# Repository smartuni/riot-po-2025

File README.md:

## GitFlow

 - [GitFlow Document] (/.github/GitFlow)

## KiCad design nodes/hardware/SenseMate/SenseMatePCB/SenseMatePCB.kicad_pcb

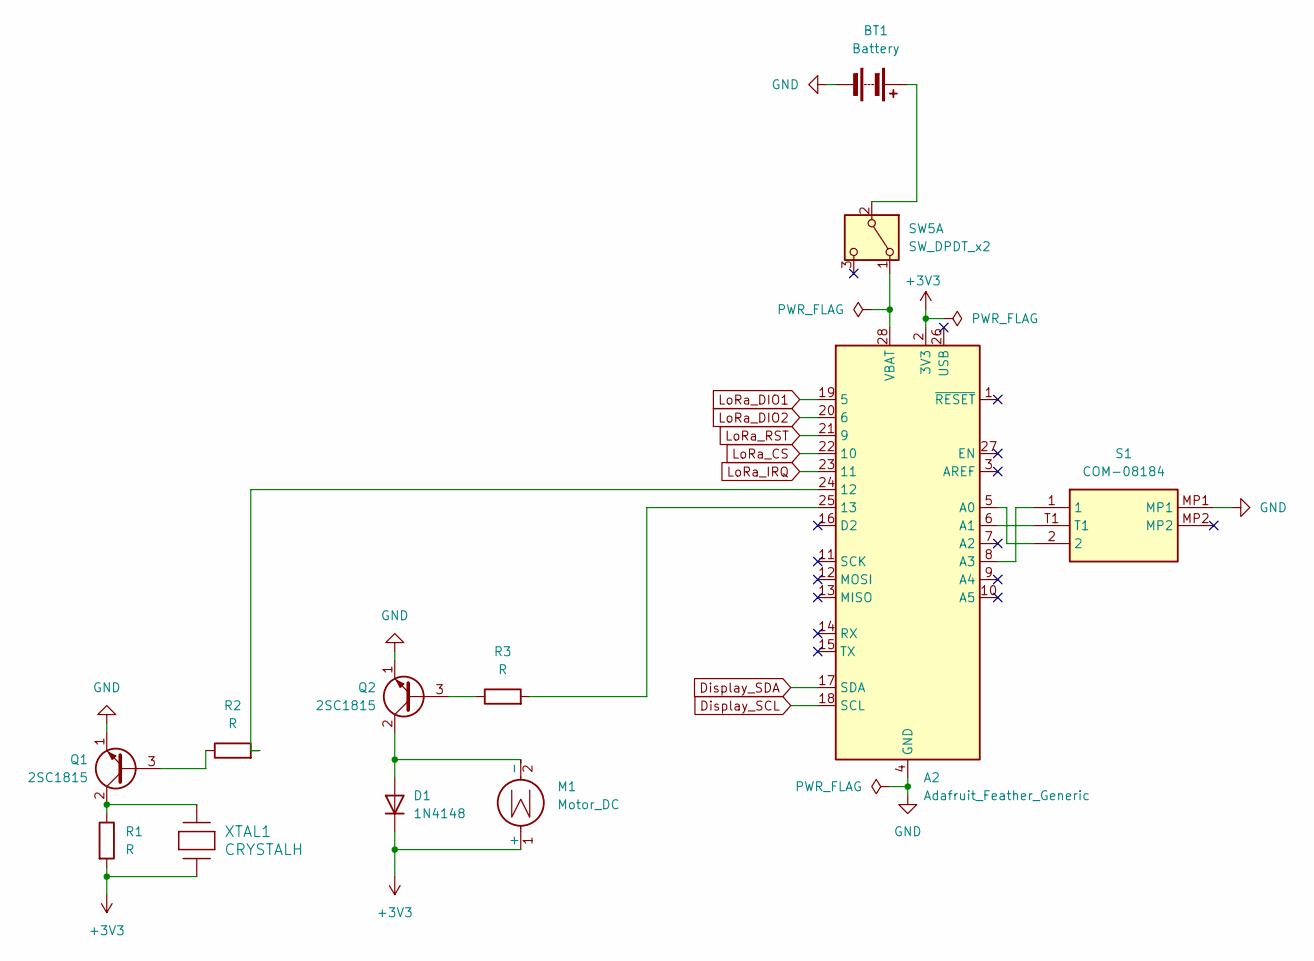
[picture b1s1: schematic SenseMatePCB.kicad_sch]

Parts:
A2: Adafruit_Feather_Generic; Adafruit_Feather_Sense
BT1: Battery; JST_PH_S2B-PH-K_1x02_P2.00mm_Horizontal
D1: 1N4148; D_DO-35_SOD27_P7.62mm_Horizontal
M1: Motor_DC; JST_PH_S2B-PH-K_1x02_P2.00mm_Horizontal
Q1, Q2: 2SC1815; TO-92_Inline
R1, R2, R3: R; R_0805_2012Metric
S1: COM-08184; COM08184; Manufacturer_Part_Number COM-08184
SW5: SW_DPDT_x2; OS102011MA1QN1
XTAL1: CRYSTALH; XTAL_PS1240P02BT_TDK

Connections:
+3V3: A2.2 (3V3), D1.1 (K), M1.1 (+), R1.2, XTAL1.1; also elsewhere on the board
GND: A2.4 (GND), BT1.2 (-), Q1.1 (E), Q2.1 (E), S1.MP1; also elsewhere on the board
LoRa_CS: A2.22 (10)
LoRa_DIO1: A2.19 (5)
LoRa_DIO2: A2.20 (6)
LoRa_IRQ: A2.23 (11)
LoRa_RST: A2.21 (9)
unnamed: A2.24 (12), R2.2
unnamed: A2.25 (13), R3.2
unnamed: A2.5 (A0), S1.2
unnamed: A2.6 (A1), S1.T1
unnamed: A2.8 (A3), S1.1
unnamed 12: A2.18 (SCL); also elsewhere on the board
unnamed 13: A2.17 (SDA); also elsewhere on the board
unnamed: A2.28 (VBAT), SW5.1 (A)
unnamed: BT1.1 (+), SW5.2 (B)
unnamed: D1.2 (A), M1.2 (-), Q2.2 (C)
unnamed: Q1.3 (B), R2.1
unnamed: Q1.2 (C), R1.1, XTAL1.2
unnamed: Q2.3 (B), R3.1

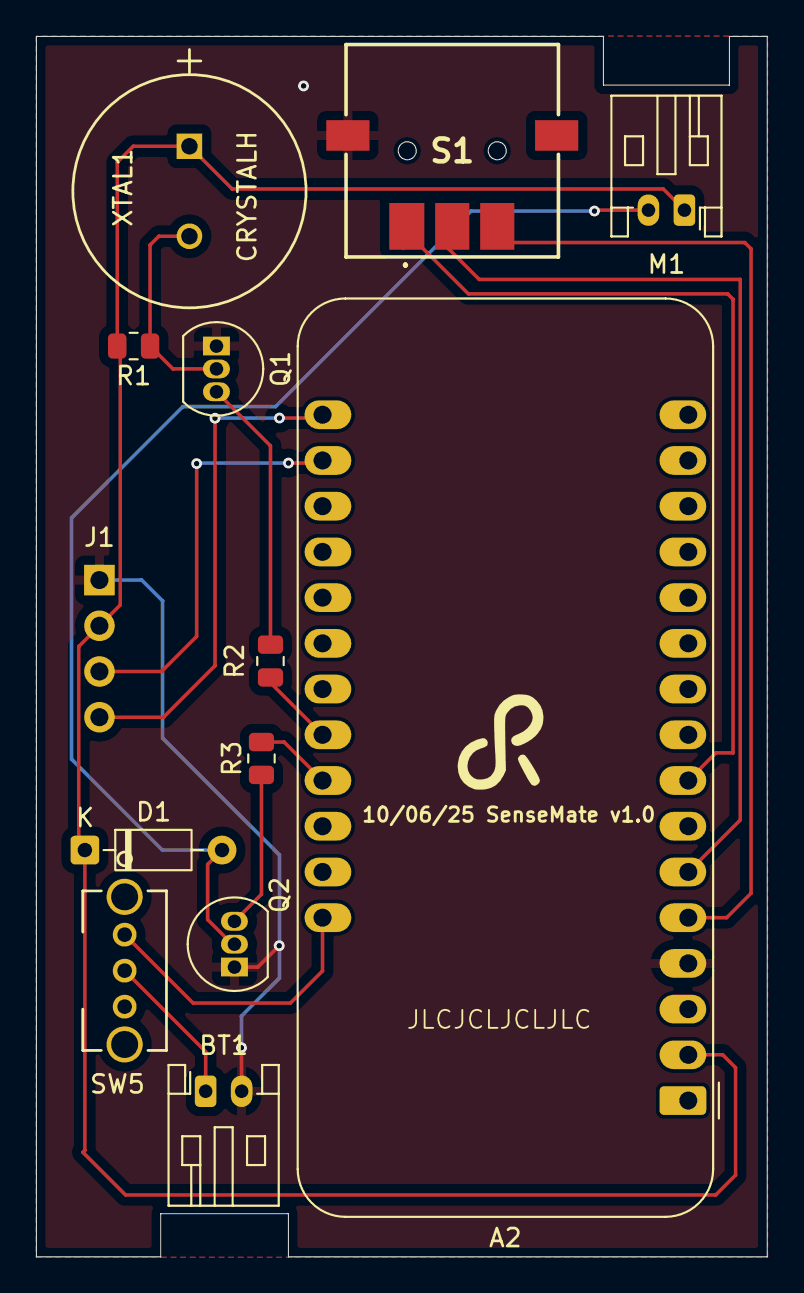
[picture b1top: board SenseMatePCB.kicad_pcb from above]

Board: 2 copper layers, 40.6 x 67.8 mm, 13 parts (1 on the bottom side), 15 nets.

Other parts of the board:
J1: Conn_01x04; PinHeader_1x04_P2.54mm_Vertical

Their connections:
+3V3: J1.2; also elsewhere on the board
GND: J1.1; also elsewhere on the board
unnamed 12: J1.3; also elsewhere on the board
unnamed 13: J1.4; also elsewhere on the board

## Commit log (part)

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2025-06-10 Node Branch update to main (#19)
    * Aufgabenverteilung
    * Notizen für Exercises
    * latest documentation
    * adjusted task for next week
    * readme moved
    * readme format fix
2025-06-10 update server branch to main (#21)
    * Update GitFlow naming of bRANCHES FOR FAK HIRACHY
    * Aufgabenverteilung
    * Reorganized initial folder structure
    * Add Readme
    * Add Heading in GateMate Readme
    * Notizen für Exercises
2025-06-10 refactored a bit; added pin header on backside for display; moved motor pin jst to side
2025-06-10 table to cbor working
2025-06-10 changed return value of tables to direct pointer
2025-06-10 menu working for gatestates
2025-06-10 modified gitignore
2025-06-10 deleted duplicated include dir
2025-06-10 resolved merge conflict
2025-06-12 Web-Team merge progress
2025-06-13 Wrote the code for confidence calculator
2025-06-15 lorawan module finished for prototype show case
2025-06-15 change board name
2025-06-15 fixes git merge errors
2025-06-15 started with 3d design for sensemate
2025-06-15 started with 3d design for sensemate #26
2025-06-15 Update: connect downlink service with HTTP-Request
2025-06-16 incoming list
2025-06-16 fixes
2025-06-16 cbor functions complete (not fully tested)
2025-06-16 fixes pt.2
2025-06-16 tables integrated
2025-06-16 fixes pt.4
2025-06-16 shit's compiling
2025-06-16 changed timeout
2025-06-16 clean up
2025-06-16 3d print ready for first sample #26
2025-06-16 added champfer on the sites #26
2025-06-16 Wrote the Confidence quality
2025-06-16 Updated ConfidenceCalculator to work with arrays of reports, allows calculator to consider more than one report
2025-06-16 cbor to table working
2025-06-16 tested sending via lorawan - not working yet!
2025-06-16 I2C FAAAST
2025-06-16 Update frontend
2025-06-16 Update: frontend latest version
2025-06-17 test 2
2025-06-22 table to cbor many tested
2025-06-22 Timer Module deleted during merge
2025-06-22 TODO
2025-06-23 second draft for sensemate casing #27
2025-06-23 Added checks to validate table entries
2025-06-23 Got rid of outmoded function, added comments
2025-06-23 Integrate local data into global table
2025-06-23 Fix table update issues
2025-06-23 Update LED indicators
2025-06-23 added activities to the UI so they are dynamic
2025-06-23 added timestamp table and done the todos for the cbor serialization
2025-06-23 Fixed problem with Status enum after merging ConfidenceCalculator branch
2025-06-23 Fixed exception with ConfidenceCalculator arrays
2025-06-23 jajaja
2025-06-23 change cose service to use external buffer to sign
2025-06-23 Fixed sizing of cbor msgs, added counter
2025-06-23 revision of pcb and 3d design #27 #28
2025-06-23 Implemented the recent acitivities with dynamic data and the dynamic notifications but not specifically for the User itself.
2025-06-23 changed motor connector to 2-pin-header
2025-06-23 Added Notification Numbers for only unread messages will decreas if u click on it and the read status in the message will change in the database to true so it wont show as ne Message again if you log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
    Also changed the alert so its a normal popup
    changed the popup so its clear to see which messages are read and which arent
2025-06-24 nodes/hardware/sensemate/sensematepcb: ordered version 1.1
2025-06-30 advertisement change and thread
2025-06-30 Fixed Security config to prevent non-logged in users making requests
2025-06-30 added table update return status
2025-06-30 Added guest view page that does not require logging in or creating an account and also added popups that prevent users from accessing the dashboard page when not logged in
2025-06-30 Fixed errors in GateService
2025-06-30 Update Readme; delete not needed main file
2025-06-30 Updating the ConfidenceCalculator
2025-06-30 Added the right functionality for the guest StatusTablesView.js
2025-06-30 Changed confidence calculation to use one universal calculator rather than each GateEntity having its own calculator
2025-06-30 added receive loop
2025-06-30 ble_send using new cbor_buffer
2025-06-30 some changes before pull
2025-06-30 For david to test
2025-06-30 receive loop ready for mergeparty
2025-06-30 debugging is_state_to_table_many method
2025-06-30 Added functionality for websocket updating of gate status instead of polling from front end
2025-06-30 structure corrected
2025-06-30 publish test keys
2025-06-30 Found out the problem with IDs, new error message :)
2025-06-30 is_state_table_to_cbor_many fixed and now working
2025-06-30 fixes for SenseGate
2025-06-30 Implement ble and working
2025-06-30 point to correct riot version
2025-06-30 refined 3d print #26
2025-07-01 Added the Priority to the GateEntity and the UI u can choose which gate should have what priority.
    Also changed the Layout of the table so we have Pending Jobs which you can change regardles off the current status and added a button for showing the activities
2025-07-01 added rssi to the tables and the encoding functions
2025-07-01 added timestamp table functions
2025-07-01 tables updatin in new_menu and displaying of headers
2025-07-01 new_menu before testing
2025-07-01 new menue workiing
2025-07-02 finished top, revised bottom
2025-07-03 Add: some changes
2025-07-03 nodes/hardware/SenseMate/SenseMate3D: drop Bak file
2025-07-03 nodes/hardware/SenseMate/SenseMate3D: update 3d design file of the SenseMate case
    *merge top and bottom part into the same file to allow referencing the same variables
    *add some tolerance definitions to compensate for imperfect 3d prints
    *improve snap fit
    *add power switch extension to compensate for too large battery/ too short PCB (shorter battery would allow smaller case)
    *add some brackets to hold the PCB and screen in place when inserted into the case
2025-07-03 nodes/hardware/SenseMate/SenseMate3D: drop old stl files and add new ones
2025-07-05 display gate menu with more info
2025-07-05 PWM testen - Include error
2025-07-05 wie ble Struktur
2025-07-05 cbor functions for timestamp_table
2025-07-06 sound module added
2025-07-06 Applied fix from is_state_table_to_cbor_many to remaining *_table_to_cbor_many functions
2025-07-06 Removed some debug output and empty lines
2025-07-06 removed empty lines
2025-07-06 priority added to payload
2025-07-06 Add Jobtable and Seentable
2025-07-06 added deleting and adding gates
2025-07-07 Fixed duplicate from merge
2025-07-07 Updating GateEntity constructors
2025-07-07 Updated the gate entity
2025-07-07 vibrating action going on HOT
2025-07-07 Fixed mqtt adding and updating gates
2025-07-07 Fixed errors from merge
2025-07-07 Frontend now updates confidence?
2025-07-07 Attempted fix for blank confidence
2025-07-07 Removed debug output, changed post event type
2025-07-07 sound threaded
2025-07-07 reset the default stacksize and configure nimBLE correctly
2025-07-07 table sending changed
2025-07-07 trigger lora on confirm
2025-07-07 working demo
2025-07-07 TTN App key
2025-07-07 Add functionality to get event when changing state of gate with mqtt
2025-07-07 Error handling for no status
2025-07-07 changes in new_menu
2025-07-07 DELETED generated ID from Entity Gate
2025-07-07 kein rssi check
2025-07-07 updated RIOT version
2025-07-07 added device_timestamp counter in tables
2025-07-08 added a helper method so the gates from the gui can be added again with the right ID
2025-07-08 Besprochene Änderungen in CBOR
2025-07-08 DEVICE_TYPE & DEVICE_ID in makefile
2025-07-09 Device ID in make-call configurable
2025-07-09 nodes/hardware/SenseMate/SenseMate3D: improve snap, increase case size a bit, improve bracket spacing
2025-07-09 display menu adjusted to tables dimensions
2025-07-09 Update Request,Ã & Pending Status, fixed timestamp
2025-07-09 Change Archiv for application yml
2025-07-09 Device type and Device ID added
2025-07-09 Introduced DownlinkCounter as Entity the DownlinkCounter will reset everyday at 00:00 if ten downlinks have been sent the button wont work anymore. if you want to reset the counter restart the server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
2025-07-10 nodes/hardware/SenseMate/logic/display: improve redraw calls to reduce screen glitches
2025-07-10 nodes/hardware/SenseMate/logic/soundModule: offload handling to thread, define sound as data
2025-07-10 nodes/hardware/SenseMate/logic/events_creation.: adjust to new sound and vibra API, remove debounce where not needed
2025-07-10 nodes/hardware/SenseMate/logic/main: adjust to new sound and vibra API, remove some dead code
2025-07-10 nodes/custom-modules/mate_ble/Makefile.include: also add id to advertised device name
2025-07-10 nodes/custom-modules/tables: improve print output on set_is_state_entry, trigger sound events on SenseMates
2025-07-10 nodes/hardware/SenseMate/logic/Makefile: add periph_pwm to USEMODULE, fix app name
2025-07-10 REMOVEME nodes/hardware/GateMate/logic/main: disable lorawan for ble testing
2025-07-10 nodes/custom-modules/mate_ble: fix RSSI filter
2025-07-10 tried to trigger sounds with events, events dont't arrive yet
2025-07-11 nodes/hardware/SenseMate/SenseMate3D: update 3D design file
2025-07-11 nodes/hardware/SenseMate/SenseMate3D: remove old design and backup files
2025-07-11 nodes/hardware/SenseMate/SenseMate3D: remove old gcode and 3mf files
2025-07-11 ignore auth_token file
2025-07-11 ignore ttn_configs
2025-07-11 add ttn_devices script
2025-07-11 cleanup and corrections
2025-07-11 Fix restarting lorawan
2025-07-11 removed wrong function call
2025-07-11 readable error
2025-07-11 cleanup
2025-07-11 updated gitignore
2025-07-11 ConfidenceCalculator considered too many reports, now considers 2 reports as opposed to 5
2025-07-11 Added some Comments not finished
2025-07-11 comments
2025-07-11 Replaced unnecessary switch case
2025-07-11 lorawanevents in EVENT_PRIO_HIGHEST
2025-07-11 close by detection
2025-07-11 stopped using the semaphore for ble advertisement to 100% avoid race condition
2025-07-11 changed the ble advertisement interval
2025-07-11 No notification to lorawan module but compilig
2025-07-11 added event handling methods
2025-07-11 fixes loraWan
2025-07-11 changed to EVENT_PRIO_MEDIUM
2025-07-11 fix is_state_table_to_cbor_many_to_server arr size
2025-07-11 rssi cooldown
2025-07-11 Rssi cooldown in UI
2025-07-12 Update Backend Readme
2025-07-13 close by disappearing fix
2025-07-13 sensegate updates its is state table every 30 seconds
2025-07-13 fix error
2025-07-13 update mqtt handler and delete todos
2025-07-13 Updteded readme
2025-07-13 timestamp of gate +=1 when sensemate input - toherwise 2nd input ignored
2025-07-13 take out test filling of tables
2025-07-13 The Requested Status and pendingJob is not set to Requested_None and Pending_none ad the creation of a gate. so the filter didnt recognized it. fixed if any issues with that go to GateService.java ad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
2025-07-13 fix of unwanted input posibility
2025-07-14 nodes readme
2025-07-14 readme hardware
2025-07-14 confidence calculator now considers three reports, does not decrease confidence with two identical reports in a row
2025-07-14 updated README of tables
2025-07-14 to table uses the MAX_GATE_COUNT for static buffer tables
2025-07-14 fixed sorting of all gates and set target to initial learning if no target
2025-07-14 nodes/RIOT: update submodule version
2025-07-14 nodes/hardware/GateMate/logic/main: reduce ble user-thread priorities
2025-07-14 nodes/custom-modules/mate_lorawan/mate_lorawan: make prints DEBUG messages, move netreg register to rx-thread
2025-07-14 odes/custom-modules/tables/tables: disable unneeded prints
2025-07-14 Added popup dialog when an uplink is received
2025-07-14 Changed timestamp for activities and added activities for sensemate
2025-07-14 fix gate 0 issue and sorting touble
2025-07-14 Added activity when new gate created
2025-07-14 mqtt location
2025-08-06 refactor nodes part of the project
2025-08-06 update paths and add comments
2025-08-06 fixed includes
2025-08-06 edited nodes readme to say signing instead of encrypting
2025-08-06 added table of contents
2025-08-06 update firmware readmes
2025-08-06 readme expandet
2025-08-06 lil cleanup
2025-08-06 documentation written
2025-08-06 removed commented out code, added explanation for ConfidenceCalculator bug during presentation
2025-08-06 added mutex for the decode cbor package function
2025-08-06 fix compile error because of wrong path
